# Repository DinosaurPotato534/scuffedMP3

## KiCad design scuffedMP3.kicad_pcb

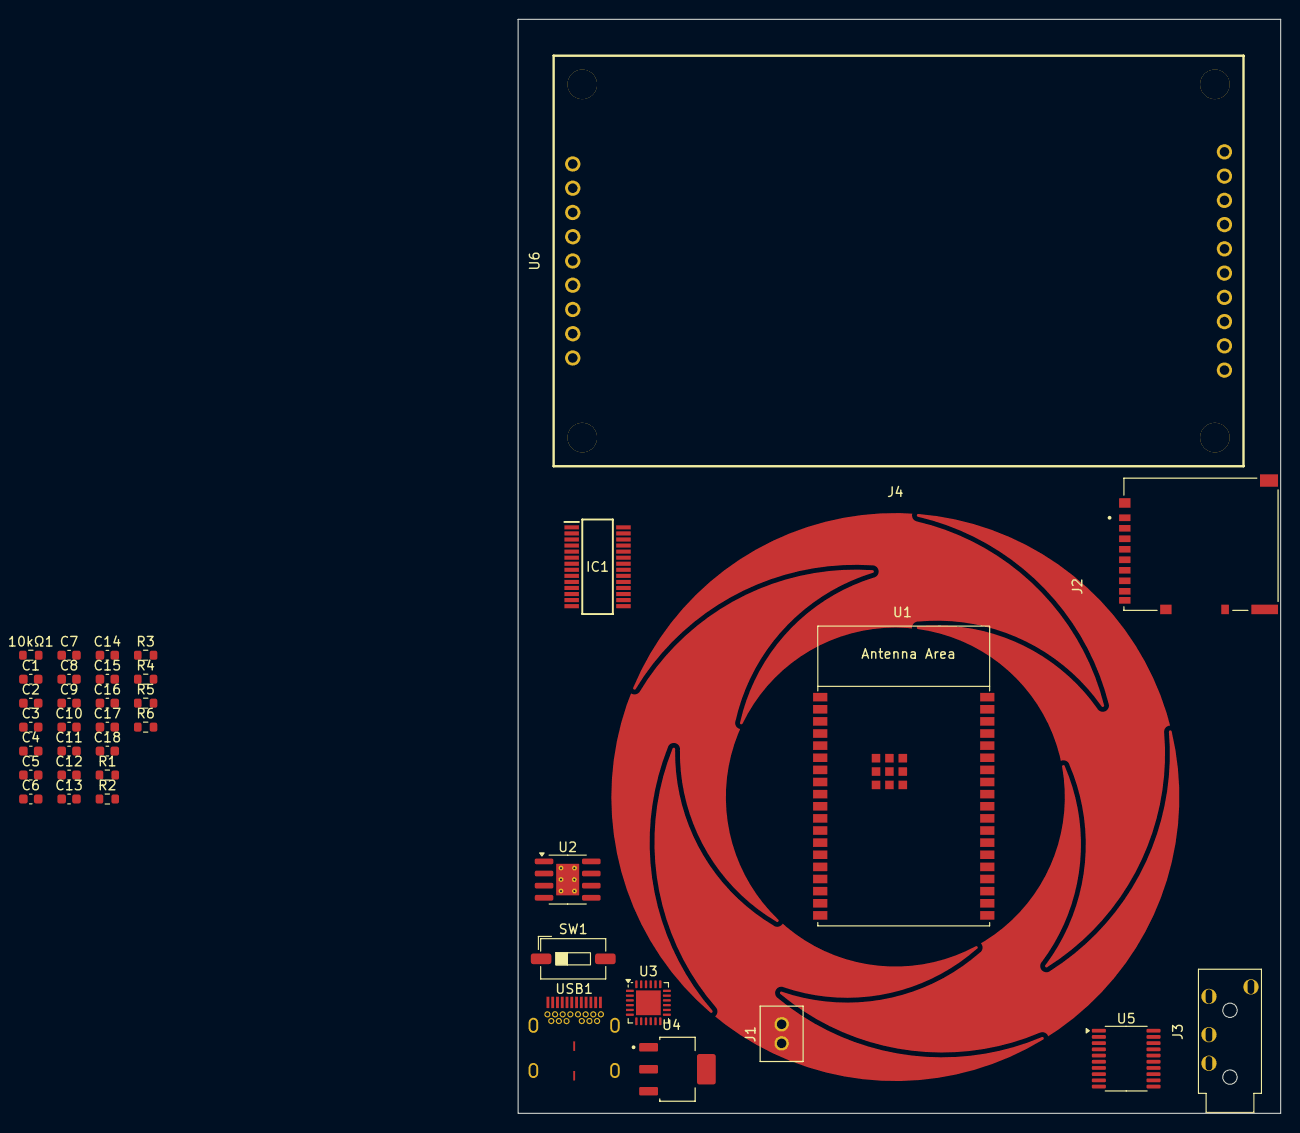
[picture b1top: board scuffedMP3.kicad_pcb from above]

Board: 2 copper layers, 79.9 x 114.6 mm, 38 parts (0 on the bottom side), 39 nets, no tracks yet.

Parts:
10kΩ1: R; R_0603_1608Metric
C1, C3, C8, C9, C10, C14, C15, C16: 1 µF; C_0603_1608Metric
C2, C4, C12, C13, C17, C18: 0.1 µF; C_0603_1608Metric
C5, C6, C7: 0.1µF; C_0603_1608Metric
C11: 0.1uF; C_0603_1608Metric
IC1: TTP229-BSF; SOP64P600X175-28N
J1: battery; JST_PHR-2
J2: DM3AT-SF-PEJM5; HRS_DM3AT-SF-PEJM5
J3: AudioJack3; PJ-320A
J4: Conn_01x16_Pin; ScrollWheel-60x35mm
R1: 10kΩ; R_0603_1608Metric
R2: 1.2 kΩ; R_0603_1608Metric
R3, R4: 10 kΩ; R_0603_1608Metric
R5, R6: 5.1 kΩ; R_0603_1608Metric
SW1: SW_SPST; SW_DIP_SPSTx01_Slide_6.7x4.1mm_W6.73mm_P2.54mm_LowProfile_J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
U1: ESP32-WROVER-E
U2: TP4056-42-ESOP8; SOIC-8-1EP_3.9x4.9mm_P1.27mm_EP2.41x3.3mm_ThermalVias
U3: CP2102N-Axx-xQFN24; QFN-24-1EP_4x4mm_P0.5mm_EP2.6x2.6mm
U4: MCP1825S; SOT230P700X180-4N
U5: PCM5102A; TSSOP-20_4.4x6.5mm_P0.65mm
U6: HS24S010B; LCD-TH_L72.3-W43.0_HS24S010B
USB1: Wurth-632723300011

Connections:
+3V3: 10kΩ1.2, C5.2, C6.2, C7.2, C11.2, C12.1, C13.1, C17.1, C18.2, IC1.9 (SENADJ3), IC1.26 (VDD), J2.4 (VDD), R1.1, R3.2, R4.2, SW1.2 (B), U1.2 (3V3), U3.6 (VDD), U5.1 (CPVDD), U5.8 (AVDD), U5.20 (DVDD), U6.2 (VCC)
/3V3 IN: C1.1, SW1.1 (A), U4.3 (VO)
/BAT: C14.2, J1.1, U2.5 (BAT)
/BOOT_SEL: 10kΩ1.1, C4.2, U1.25 (GPIO0/BOOT/ADC2_CH1)
/Bit Clock: U1.11 (DAC_2/ADC2_CH9/GPIO26), U5.13 (BCK)
/DAC DIN: U1.36 (GPIO22), U5.14 (DIN)
/EN: C2.1, R1.2, U1.3 (EN/CHIP_PU)
/LR CLOCK: U1.10 (DAC_1/ADC2_CH8/GPIO25), U5.15 (LRCK)
/MICRO CLK: J2.5 (CLK), U1.24 (ADC2_CH2/GPIO2)
/MICRO CMD: J2.3 (CMD), U1.26 (ADC2_CH0/GPIO4)
/MICRO DAT0: J2.7 (DAT0), U1.8 (32K_XP/GPIO32/ADC1_CH4)
/MOSI OLED: U1.37 (GPIO23), U6.4 (SDA)
/OLED CS: U1.29 (GPIO5), U6.7 (CS)
/OLED DC: U1.12 (ADC2_CH7/GPIO27), U6.6 (DC)
/OLED LED: U1.33 (GPIO21), U6.8 (LED)
/OLED RST: U1.31 (GPIO19), U6.11 (RST)
/OLED SCL: U1.30 (GPIO18), U6.3 (SCL)
/TOUCH SCL: IC1.13 (SCL), U1.9 (32K_XN/GPIO33/ADC1_CH5)
/TOUCH TP0: IC1.6 (TP0), J4.1
/TOUCH TP1: IC1.5 (TP1), J4.2
/TOUCH TP2: IC1.2 (TP2), J4.3
/TOUCH TP3: IC1.1 (TP3), J4.4
/TOUCH TP4: IC1.25 (TP4), J4.5
/UART_RXD: U1.34 (U0RXD/GPIO3), U3.20 (RXD)
/UART_TXD: U1.35 (U0TXD/GPIO1), U3.21 (TXD)
GND: C1.2, C3.2, C5.1, C6.1, C7.1, C8.2, C9.2, C10.2, C11.1, C12.2, C13.2, C14.1, C15.2, C16.1, C17.2, C18.1, IC1.4 (SENADJ0), IC1.14 (SLPSENB), IC1.17 (SENADJ2), IC1.20 (TEST), IC1.23 (SENADJ1), IC1.27 (VSS), J1.2, J2.6 (VSS), J2.P1 (SHIELD), J2.P2 (SHIELD), J2.P3 (SHIELD), J2.P4 (SHIELD), J3.S, R2.2, R5.2, R6.2, U1.1 (GND), U1.15 (GND), U1.38 (GND), U2.3 (GND), U3.2 (GND), U3.25 (GND), U4.2 (GND), U5.3 (CPGND), U5.9 (AGND), U5.16 (FMT), U5.17 (XSMT), U5.19 (DGND), U6.1 (GND), USB1.1 (GND), USB1.12 (GND), USB1.13 (GND), USB1.24 (GND), USB1.25 (Center_Plate_Pin), USB1.26 (Connector_Legs), USB1.27 (Under-Barrel_Pads)
unnamed: IC1.28 (SLPSENA), R4.1
unnamed: R2.1, U2.2 (PROG)
unnamed: C2.2, U3.23 (~DTR)
unnamed: R3.1, U3.9 (~RST)
unnamed: C4.1, U3.19 (~RTS)
unnamed: C8.1, U5.4 (CAPM)
unnamed: C10.1, U5.2 (CAPP)
unnamed: J3.T, U5.6 (OUTL)
unnamed: J3.R, U5.7 (OUTR)
unnamed: C9.1, U5.5 (VNEG)
unnamed: R5.1, USB1.5 (CC1)
unnamed: R6.1, USB1.17 (CC2)
VBUS: C3.1, C15.1, C16.2, U2.4 (V_{CC}), U2.8 (CE), U3.7 (VREGIN), U3.8 (VBUS), U4.1 (VI), USB1.4 (VBUS), USB1.9 (VBUS), USB1.16 (VBUS), USB1.21 (VBUS)

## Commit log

2025-03-29 we are going to explode
2025-03-29 added screen
2025-03-29 addded adc
2025-03-29 firmware
2025-03-29 added new cpu
2025-03-29 code v2
2025-05-04 schematic (scuffed)
2025-05-05 add touch sensor and wheel
2025-05-10 Scroll wheel
    sorry mate was not able to finish design fully :(
2025-05-10 Revert "Scroll wheel"
    This reverts commit 91615402a06c605ac7a87ecd01782970de634324.
2025-05-12 progress
